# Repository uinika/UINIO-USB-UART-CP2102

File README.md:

# UINIO-USB-UART-CP2102 串口调试器

[**UINIO-USB-UART-CP2102**](https://gitee.com/uinika/UINIO-USB-UART-CP2102) 是一款基于 [**美国芯科 CP2102**](https://www.silabs.com/interface/usb-bridges/classic/device.cp2102) 芯片的 **USB** 转 **UART** 的开源串口调试器，该款芯片采用 `QFN28` 封装，可以稳定支持 `921600` 波特率的 UART 串口通信。

## 设计概要

1. 板载 `RXD` 和 `TXD` 的信号传输状态指示灯；
2. USB 信号线上并入了两枚 TVS 瞬态电压抑制二极管；
3. 引出了包括**串口硬件流控信号线**在内的全部片上资源；
4. 为 `5V` 输出提供了**自恢复保险丝**和**二极管**组成的防反接保护电路；
5. 预留有 `2mm` 的固定螺丝孔，便于安装至 3D 打印外壳，或者搭建成套的产品原型；

## 参考技术文档

[UinIO.com 电子技术实验室](http://uinio.com/) 为 **UINIO-USB-UART-CP2102** 开源项目提供了如下一系列技术参考资料：

- [《UINIO-DAPLink 核心板原理图》](http://uinio.com/my/works/UINIO-USB-UART-CP2102/UINIO-USB-UART-CP2102-Schematic.pdf)
- [《交互式 BOM 物料清单与 PCB 版图在线预览》](http://uinio.com/my/works/UINIO-USB-UART-CP2102/UINIO-USB-UART-CP2102-BOM.html)

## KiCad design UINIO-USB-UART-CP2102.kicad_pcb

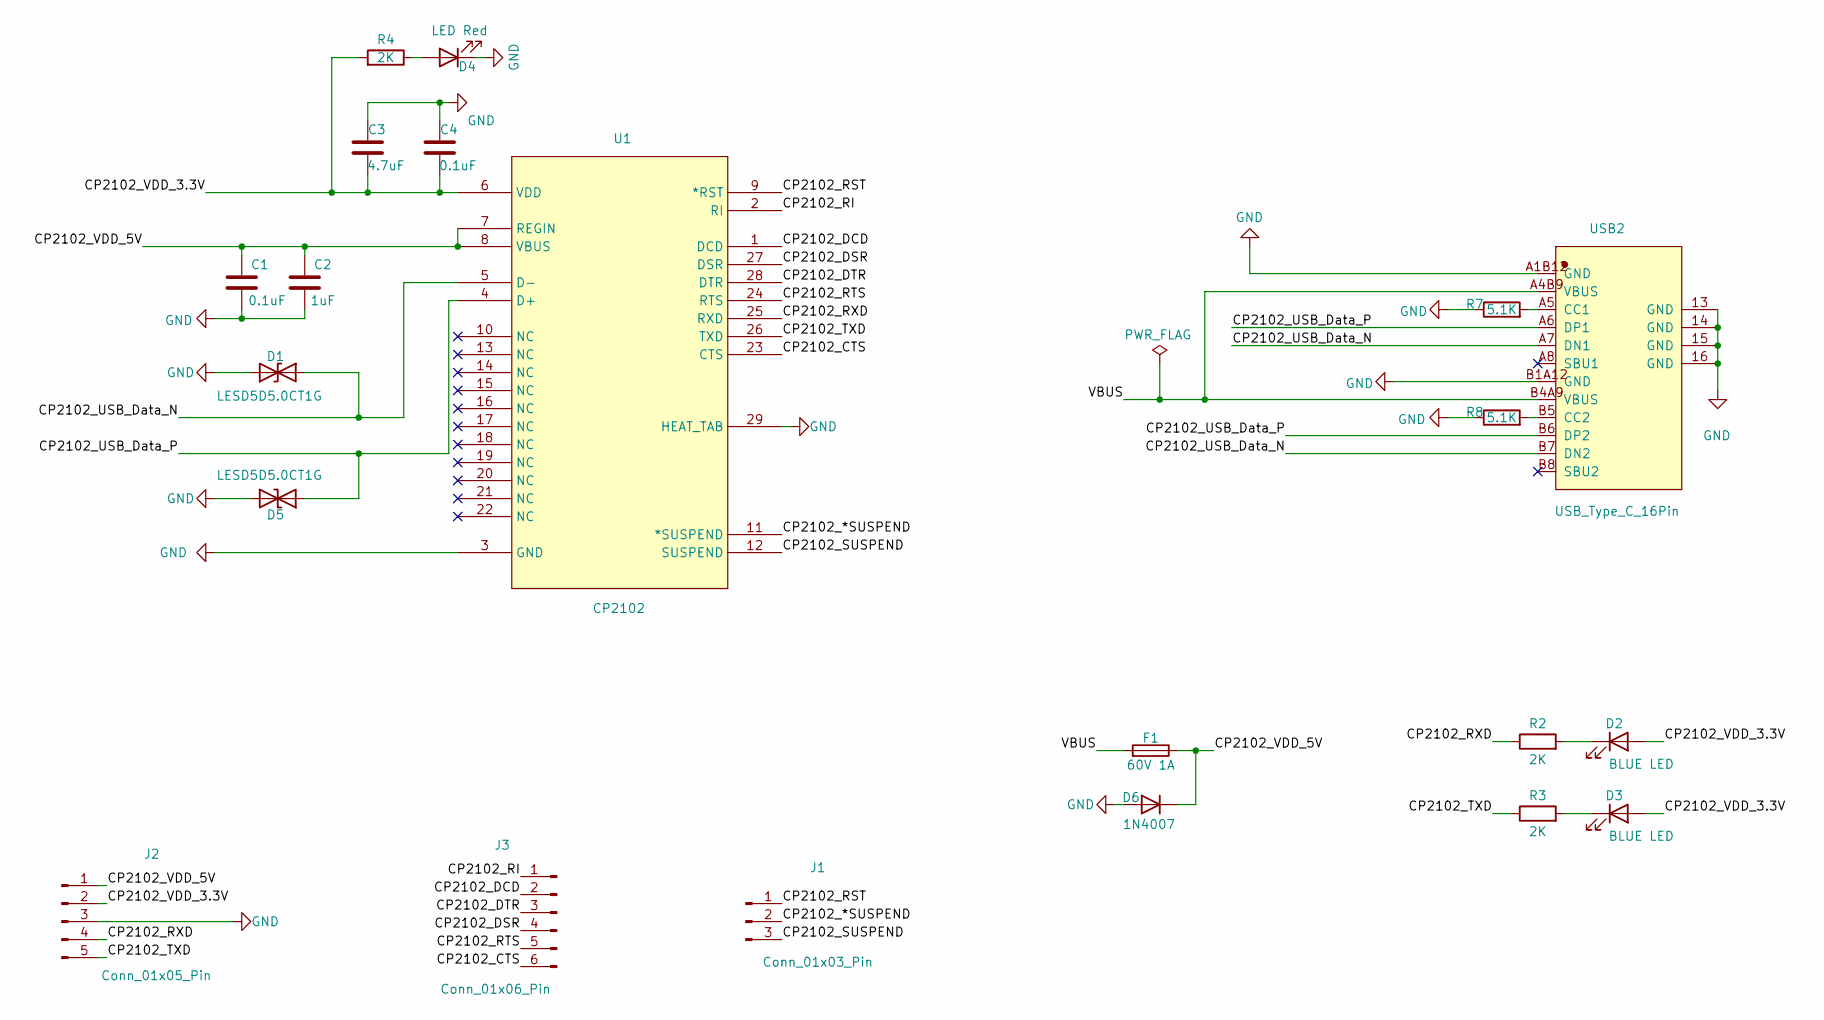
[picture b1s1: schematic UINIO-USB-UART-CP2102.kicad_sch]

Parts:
C1, C4: 0.1uF; C_0402_1005Metric
C2: 1uF; C_0402_1005Metric
C3: 4.7uF; C_0402_1005Metric
D1, D5: LESD5D5.0CT1G; D_SOD-523
D2, D3: BLUE LED; LED_0603_1608Metric
D4: LED Red; LED_0603_1608Metric
D6: 1N4007; Nexperia_CFP3_SOD-123W
F1: 60V 1A; Fuse_1206_3216Metric
J1: Conn_01x03_Pin; PinHeader_1x03_P2.54mm_Vertical
J2: Conn_01x05_Pin; PinHeader_1x05_P2.54mm_Vertical
J3: Conn_01x06_Pin; PinHeader_1x06_P2.54mm_Vertical
R2, R3, R4: 2K; R_0603_1608Metric
R7, R8: 5.1K; R_0603_1608Metric
U1: CP2102; QFN-28_L5.0-W5.0-P0.50-TL-EP3.3; MFG #1 SILICON LABS
USB2: USB_Type_C_16Pin; USB-C-SMD_TYPEC-304J-BCP16

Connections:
/CP2102_*SUSPEND: J1.2, U1.11 (*SUSPEND)
/CP2102_CTS: J3.6, U1.23 (CTS)
/CP2102_DCD: J3.2, U1.1 (DCD)
/CP2102_DSR: J3.4, U1.27 (DSR)
/CP2102_DTR: J3.3, U1.28 (DTR)
/CP2102_RI: J3.1, U1.2 (RI)
/CP2102_RST: J1.1, U1.9 (*RST)
/CP2102_RTS: J3.5, U1.24 (RTS)
/CP2102_RXD: J2.4, R2.1, U1.25 (RXD)
/CP2102_SUSPEND: J1.3, U1.12 (SUSPEND)
/CP2102_TXD: J2.5, R3.1, U1.26 (TXD)
/CP2102_USB_Data_N: D1.2 (A2), U1.5 (D-), USB2.A7 (DN1), USB2.B7 (DN2)
/CP2102_USB_Data_P: D5.2 (A2), U1.4 (D+), USB2.A6 (DP1), USB2.B6 (DP2)
/CP2102_VDD_3.3V: C3.1, C4.1, D2.2 (A), D3.2 (A), J2.2, R4.2, U1.6 (VDD)
/CP2102_VDD_5V: C1.1, C2.1, D6.1 (K), F1.1, J2.1, U1.7 (REGIN), U1.8 (VBUS)
/VBUS: F1.2, USB2.A4B9 (VBUS), USB2.B4A9 (VBUS)
GND: C1.2, C2.2, C3.2, C4.2, D1.1 (A1), D4.1 (K), D5.1 (A1), D6.2 (A), J2.3, R7.1, R8.1, U1.3 (GND), U1.29 (HEAT_TAB), USB2.13 (GND), USB2.14 (GND), USB2.15 (GND), USB2.16 (GND), USB2.A1B12 (GND), USB2.B1A12 (GND)
unnamed: D2.1 (K), R2.2
unnamed: D3.1 (K), R3.2
unnamed: D4.2 (A), R4.1
unnamed: R7.2, USB2.A5 (CC1)
unnamed: R8.2, USB2.B5 (CC2)

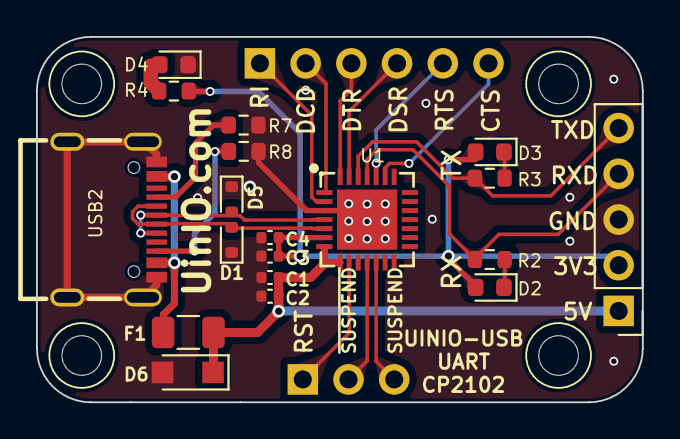
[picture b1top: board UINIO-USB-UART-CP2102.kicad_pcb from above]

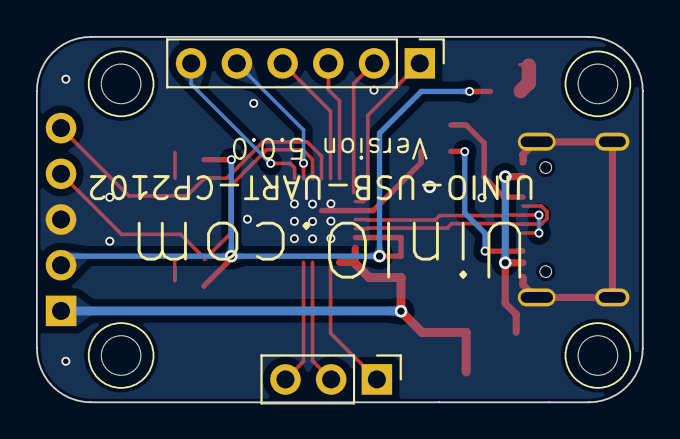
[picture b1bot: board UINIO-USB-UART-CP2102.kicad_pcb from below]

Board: 2 copper layers, 33.7 x 20.3 mm, 25 parts (2 on the bottom side), 22 nets.

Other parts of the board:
HOLE**: Hole-2mm
HOLE**#2, HOLE**#3, HOLE**#4: Hole-2mm

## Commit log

2024-11-25 Release UINIO-USB-UART-CP2102 version 5.0.0.
